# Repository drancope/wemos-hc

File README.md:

# This is first basic info for a Wemos Home Control project.
The first atempt was built in summer 2020, controls two ceiling lamps, and uses a wemos wired to the main door switches and to a kicad home made PCB with a pair of opto-couplers (moc3121) and triacs (bt136). It's been working for a year with only two reset problemas, before I engage in this description of the project and an improved design.
Two more wemos are also used to emit wifi orders (post http method). These ones are placed in the bed sides for convenience.
The main server creates its own local wifi lan, and mobile phones can get an ip and access the wemos web server, displaying a page where the user can turn on/off the lights.
Code is based on ESP8266 examples

# Goals:
- learning and experimenting with mc and electronics
 -- programming servers, use of wifi libraries
 -- making PCBs with power devices

- use of wemos minicontrollers to switch lights at home,
  -- server to accept mobile orders
  -- reliable if home router fails
  -- initially, does not depend on iot standards, but considering learning about that.
  
- Expandable
 -- accepting internet orders
   --- a second wemos wired to main wemos, to provide connection to local network.
   --- future use of cloud computing, or aws iot messages.

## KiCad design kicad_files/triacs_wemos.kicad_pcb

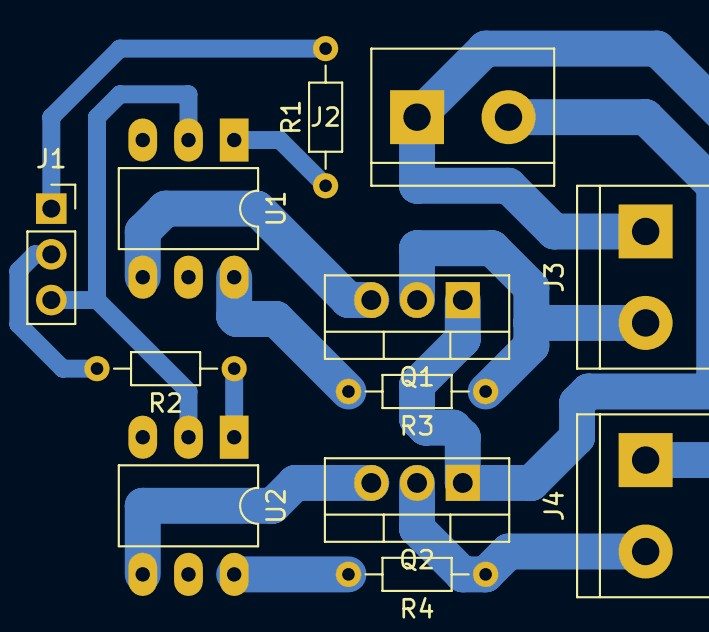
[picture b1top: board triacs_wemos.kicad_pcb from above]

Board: 2 copper layers, 12 parts (0 on the bottom side), 13 nets.

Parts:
J1: Wemos; PinSocket_1x03_P2.54mm_Vertical
J2: Alim-altern; TerminalBlock_bornier-2_P5.08mm
J3: Luz 1; TerminalBlock_bornier-2_P5.08mm
J4: Luz 2; TerminalBlock_bornier-2_P5.08mm
Q1, Q2: BT136-600; TO-220-3_Vertical
R1, R2, R3, R4: R; R_Axial_DIN0204_L3.6mm_D1.6mm_P7.62mm_Horizontal
U1, U2: MOC3021M; DIP-6_W7.62mm_LongPads

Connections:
GND: J1.3, U1.2, U2.2
unnamed: J1.1, R1.2
unnamed: J1.2, R2.2
unnamed: J2.1, J3.1, J4.1
unnamed: J2.2, Q1.1, Q2.1
unnamed: J3.2, Q1.2, R3.1
unnamed: J4.2, Q2.2, R4.1
unnamed: Q1.3, U1.4
unnamed: Q2.3, U2.4
unnamed: R1.1, U1.1
unnamed: R2.1, U2.1
unnamed: R3.2, U1.6
unnamed: R4.2, U2.6

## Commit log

2021-05-27 Creación del proyecto
2021-05-27 Home lights control with wemos
    Switching circuits with triacs and opto-couplers.
    Both, Post server and client wemos controllers.
